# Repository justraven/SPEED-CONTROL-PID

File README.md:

# MOTOR DC SPEED CONTROL

Implementing PID control to regulate the speed of a DC motor.

## File Structure
```
📦CODE
 ┣ 📂lib
 ┃ ┣ 📂parsing
 ┃ ┃ ┗ 📜parsing.h
 ┣ 📂src
 ┃ ┗ 📜main.cpp
 📦GUI
 ┣ 📂LABVIEW
 ┃ ┣ 📜block_diagram.pdf
 ┃ ┣ 📜block_diagram_2.pdf
 ┃ ┣ 📜block_diagram_3.pdf
 ┃ ┣ 📜front_panel.pdf
 ┃ ┣ 📜front_panel_2.pdf
 ┃ ┣ 📜front_panel_3.pdf
 ┃ ┣ 📜GUI.vi
 ┃ ┣ 📜GUI_SubVi.vi
 ┃ ┣ 📜PID.txt
 ┃ ┣ 📜PID_2.txt
 ┃ ┣ 📜PID_3.txt
 ┃ ┗ 📜TEST.txt
 ┗ 📂LABVIEW LEGACY
 ┃ ┣ 📂GUI v2
 ┃ ┃ ┗ 📜GUI.vi
 ┃ ┣ 📂GUI v2.1
 ┃ ┃ ┗ 📜GUI.vi
 ┃ ┗ 📜GUI.vi
📦3D Case Design
 ┗ 📂Desain Mekanik Kendali Motor DC
 ┃ ┣ 📜Alas untuk Motor DC.DXF
 ┃ ┣ 📜Alas untuk Motor DC.SLDPRT
 ┃ ┣ 📜Couple Motor.jpeg
 ┃ ┣ 📜Desain Mekanik V1 Atas.PNG
 ┃ ┣ 📜Desain Mekanik V1 Depan.PNG
 ┃ ┣ 📜Desain Mekanik V1 Trimetric kiri.PNG
 ┃ ┣ 📜Desain Mekanik V1 Trimetric.PNG
 ┃ ┣ 📜Desain Mekanik V2 Atas.PNG
 ┃ ┣ 📜Desain Mekanik V2 Trimetric.PNG
 ┃ ┣ 📜Desain Mekanik V3 Atas.PNG
 ┃ ┣ 📜Desain Mekanik V3 Trimetric.PNG
 ┃ ┣ 📜holder motor dc.PNG
 ┃ ┣ 📜Holder Motor DC.SLDPRT
 ┃ ┣ 📜Holder Motor DC.STL
 ┃ ┣ 📜Kendali Motor DC.SLDASM
 ┃ ┣ 📜motor masuk holder.jpeg
 ┃ ┣ 📜Spacer.SLDPRT
 ┃ ┣ 📜SPEED CONTROL MOTOR DC.SLDASM
 ┃ ┣ 📜SPEED_CONTROL_2.step
 ┃ ┣ 📜SPEED_CONTROL_NEW.step
 ┃ ┗ 📜Terminal block TB-1503.SLDASM
 ```
 
## Software Used
- Vscode (with platformio extension)
- LabVIEW (for GUI, I use LabView 21)
- KiCad (I use ver 6.0.10)
- SolidWorks (for 3D modeling)

## Developed by
- Alim Satria [@justraven](https://github.com/justraven) (PCB Design, Firmware)
- Ilham Dwi Cahyo [@ilhamdwi754](https://github.com/ilhamdwi754) (3D Design)

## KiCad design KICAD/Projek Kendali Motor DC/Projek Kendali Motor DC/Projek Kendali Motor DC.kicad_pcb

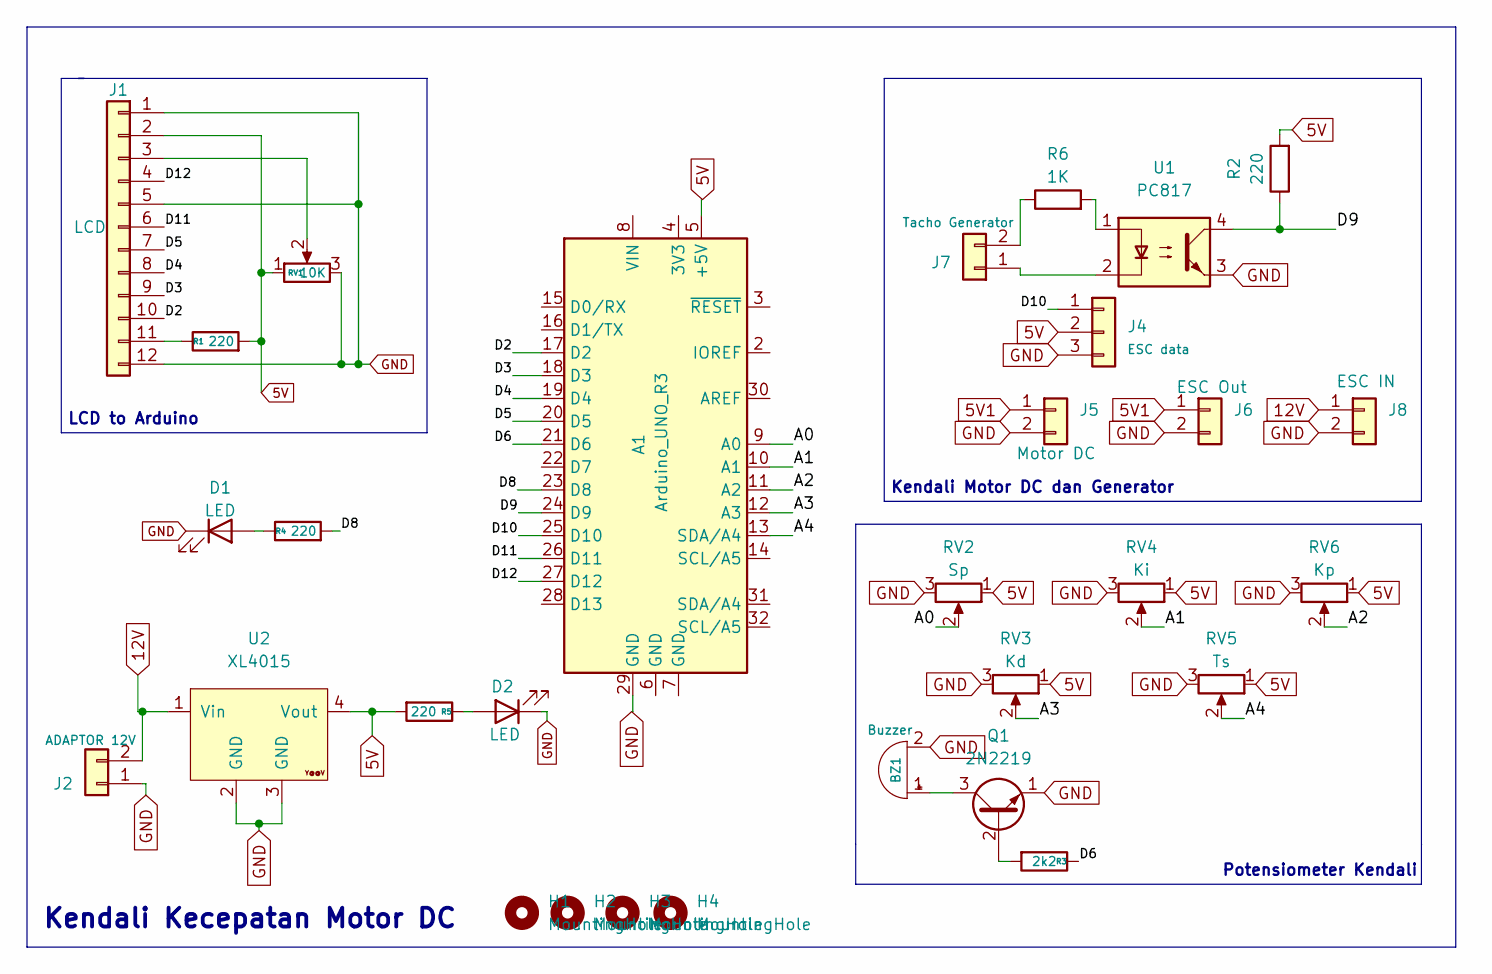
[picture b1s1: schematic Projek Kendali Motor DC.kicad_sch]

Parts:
A1: Arduino_UNO_R3; Arduino_UNO_R3_WithMountingHoles
BZ1: Buzzer; Buzzer_12x9.5RM7.6
D1, D2: LED; LED_D5.0mm
H1, H2, H3, H4: MountingHole; MountingHole_2.5mm_Pad_Via
J1: LCD; PinHeader_1x12_P2.54mm_Vertical
J2: ADAPTOR 12V; TerminalBlock_bornier-2_P5.08mm
J4: ESC data; PinHeader_1x03_P2.54mm_Vertical
J5: Motor DC; TerminalBlock_bornier-2_P5.08mm
J6: ESC Out; TerminalBlock_bornier-2_P5.08mm
J7: Tacho Generator; TerminalBlock_bornier-2_P5.08mm
J8: ESC IN; TerminalBlock_bornier-2_P5.08mm
Q1: 2N2219; TO-39-3
R1, R2, R4, R5: 220; R_Axial_DIN0207_L6.3mm_D2.5mm_P7.62mm_Horizontal
R3: 2k2; R_Axial_DIN0207_L6.3mm_D2.5mm_P7.62mm_Horizontal
R6: 1K; R_Axial_DIN0207_L6.3mm_D2.5mm_P7.62mm_Horizontal
RV1: 10K; Potentiometer_Piher_PC-16_Single_Horizontal
RV2: Sp; Potentiometer_Piher_PC-16_Single_Horizontal
RV3: Kd; Potentiometer_Piher_PC-16_Single_Horizontal
RV4: Ki; Potentiometer_Piher_PC-16_Single_Horizontal
RV5: Ts; Potentiometer_Piher_PC-16_Single_Horizontal
RV6: Kp; Potentiometer_Piher_PC-16_Single_Horizontal
U1: PC817; DIP-4_W7.62mm
U2: XL4015; YAAJ_DCDC_StepDown_LM2596

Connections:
5V: A1.5 (+5V), J1.2, J4.2, R1.2, R2.2, R5.2, RV1.1, RV2.1, RV3.1, RV4.1, RV5.1, RV6.1, U2.4 (Vout); also elsewhere on the board
5V1: J5.1, J6.1
12V: J2.2, J8.1, U2.1 (Vin)
/A0: A1.9 (A0), RV2.2
/A1: A1.10 (A1), RV4.2
/A2: A1.11 (A2), RV6.2
/A3: A1.12 (A3), RV3.2
/A4: A1.13 (SDA/A4), RV5.2
/D2: A1.17 (D2), J1.10
/D3: A1.18 (D3), J1.9
/D4: A1.19 (D4), J1.8
/D5: A1.20 (D5), J1.7
/D6: A1.21 (D6), R3.1
/D8: A1.23 (D8), R4.2
/D9: A1.24 (D9), R2.1, U1.4
/D10: A1.25 (D10), J4.1
/D11: A1.26 (D11), J1.6
/D12: A1.27 (D12), J1.4
GND: A1.29 (GND), BZ1.2 (+), D1.1 (K), D2.1 (K), J1.1, J1.5, J1.12, J2.1, J4.3, J5.2, J6.2, J8.2, Q1.1 (E), RV1.3, RV2.3, RV3.3, RV4.3, RV5.3, RV6.3, U1.3, U2.2 (GND), U2.3 (GND); also elsewhere on the board
unnamed: BZ1.1 (-), Q1.3 (C)
unnamed: D1.2 (A), R4.1
unnamed: D2.2 (A), R5.1
unnamed: J1.3, RV1.2
unnamed: J1.11, R1.1
unnamed: J7.2, R6.1
unnamed: Q1.2 (B), R3.2
unnamed: R6.2, U1.1
unnamed: J7.1, U1.2

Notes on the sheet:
Kendali Kecepatan Motor DC
Kendali Motor DC dan Generator
LCD to Arduino
Potensiometer Kendali

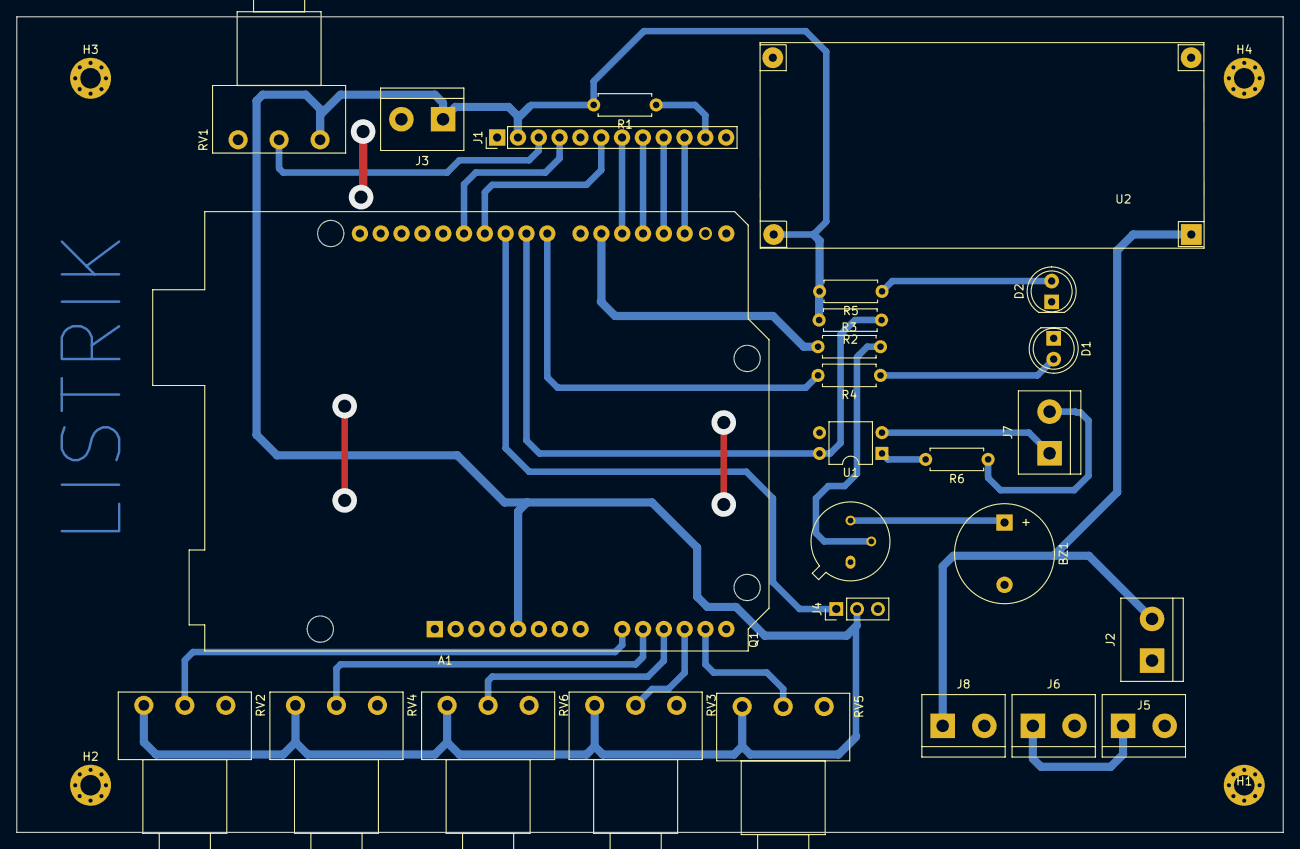
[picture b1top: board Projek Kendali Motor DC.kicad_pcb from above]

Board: 2 copper layers, 154.5 x 99.5 mm, 31 parts (0 on the bottom side), 28 nets.

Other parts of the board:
J3: Stepdown OUT; TerminalBlock_bornier-2_P5.08mm

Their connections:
5V: J3.1; also elsewhere on the board
GND: J3.2; also elsewhere on the board

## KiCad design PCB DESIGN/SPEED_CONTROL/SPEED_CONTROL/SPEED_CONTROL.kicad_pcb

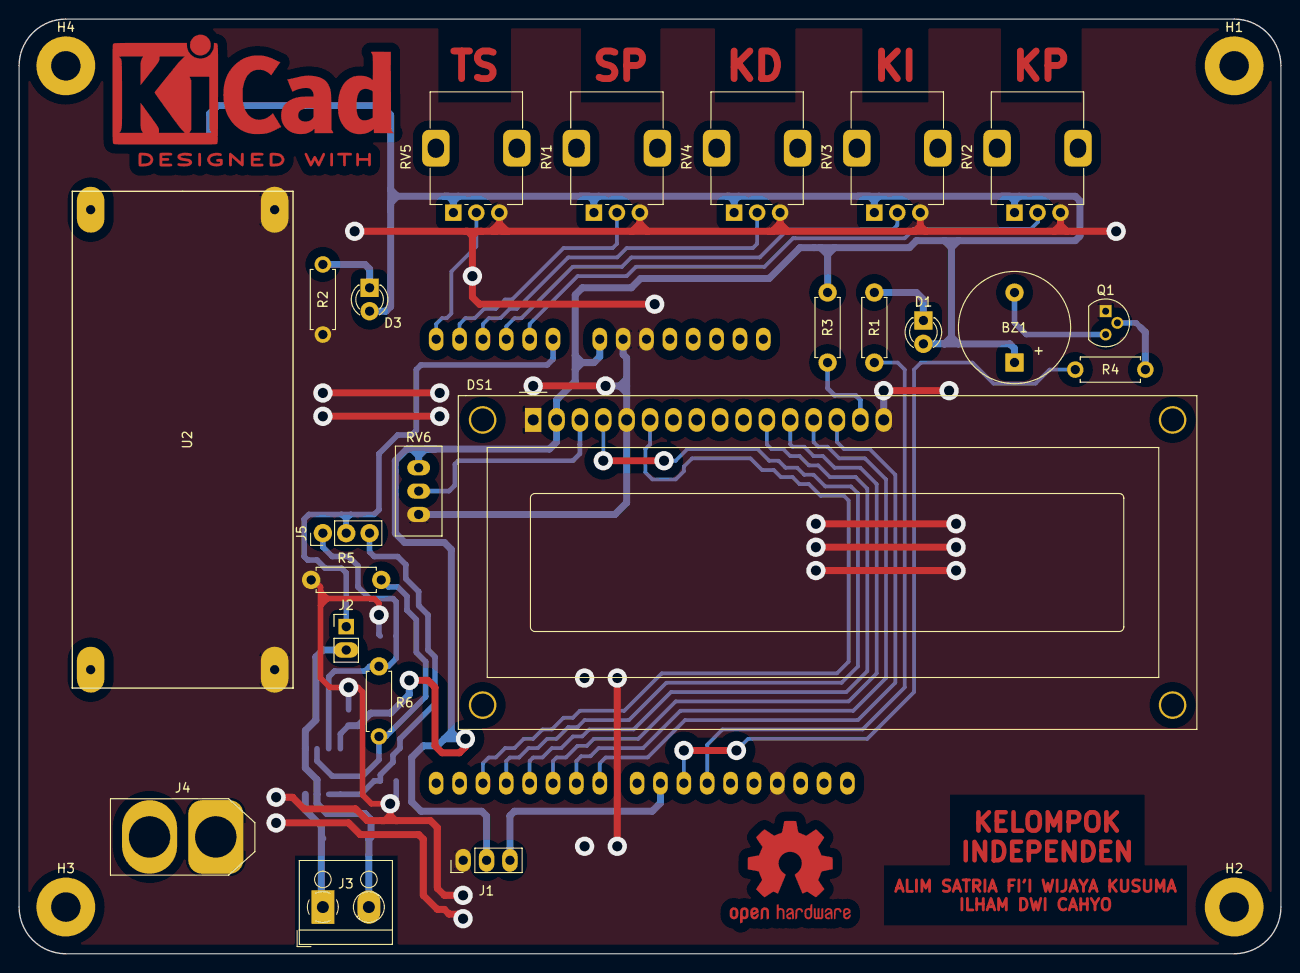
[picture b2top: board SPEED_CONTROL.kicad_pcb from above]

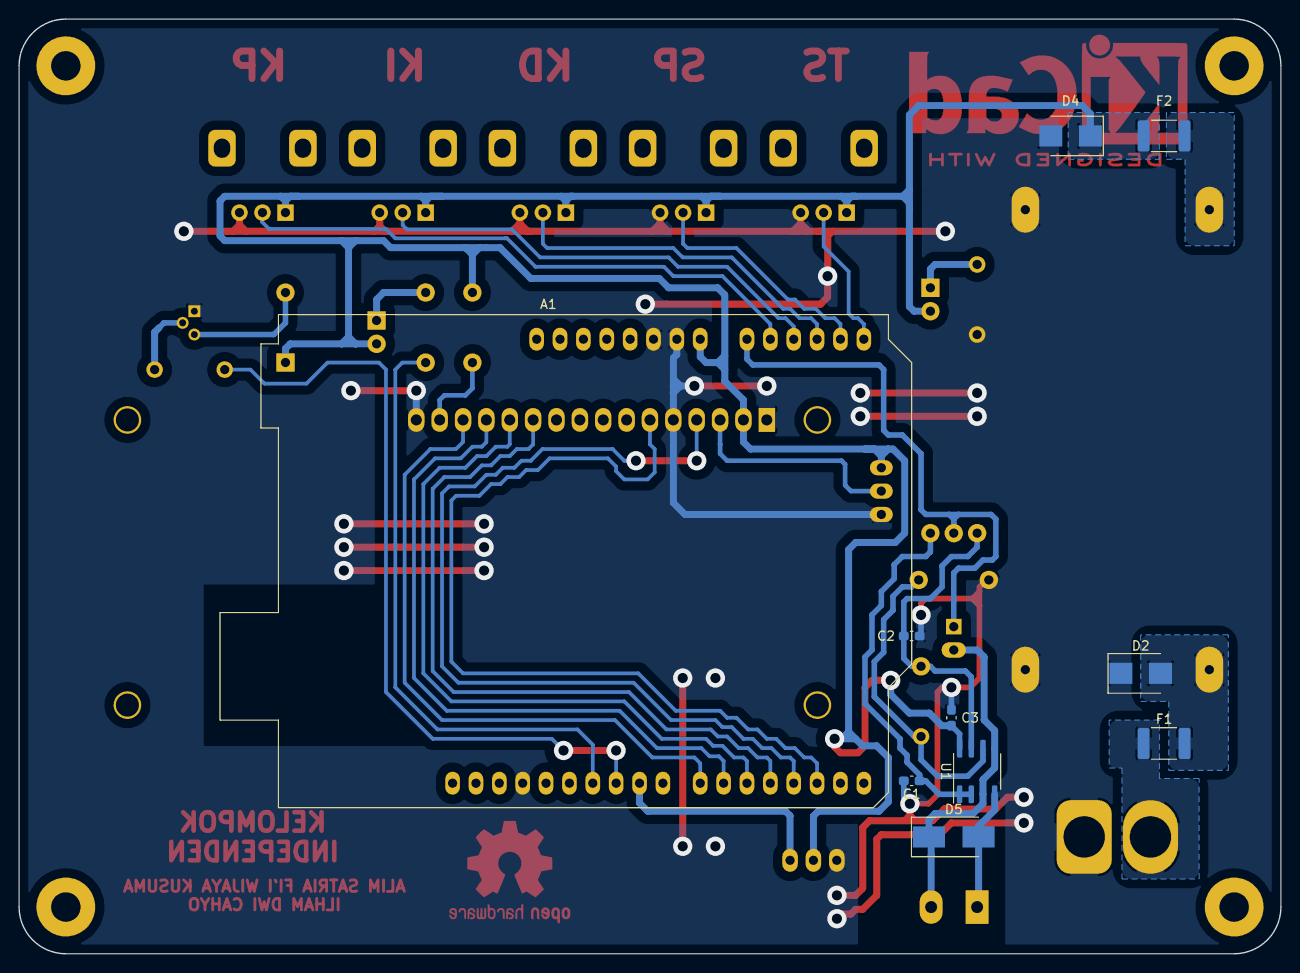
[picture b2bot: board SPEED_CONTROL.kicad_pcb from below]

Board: 2 copper layers, 137.2 x 101.6 mm, 37 parts (10 on the bottom side), 30 nets.

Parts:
A1: Arduino_UNO_R3
BZ1: Buzzer; MagneticBuzzer_ProSignal_ABI-009-RC
C1, C2: 0.1uF/100nF; C_0603_1608Metric_Pad1.08x0.95mm_HandSolder
C3: 0.1uF / 100nF; C_0603_1608Metric_Pad1.08x0.95mm_HandSolder
D1, D3: LED; LED_D3.0mm
D2: DIODE; D_SMB
D4: D; D_SMB
D5: D_Small; D_SMB_Handsoldering
DS1: WC1602A
F1: 16V/2A; Fuse_1812_4532Metric_Pad1.30x3.40mm_HandSolder
F2: 16V/02A; Fuse_1812_4532Metric_Pad1.30x3.40mm_HandSolder
H1, H2, H3, H4: MountingHole; MountingHole_3.2mm_M3_Pad
J1: ESC_PIN; PinHeader_1x03_P2.54mm_Vertical
J2: SEN_PIN; PinHeader_1x02_P2.54mm_Vertical
J3: Screw_Terminal_01x02; TerminalBlock_RND_205-00001_1x02_P5.00mm_Horizontal
J4: POWER CONN; AMASS_XT60-M_1x02_P7.20mm_Vertical
J5: SWITCH_SEN; PinHeader_1x03_P2.54mm_Vertical
Q1: 2N222; TO-92
R1, R2, R3: 330R; R_Axial_DIN0207_L6.3mm_D2.5mm_P7.62mm_Horizontal
R4: 1K; R_Axial_DIN0207_L6.3mm_D2.5mm_P7.62mm_Horizontal
R5: 10K; R_Axial_DIN0207_L6.3mm_D2.5mm_P7.62mm_Horizontal
R6: 20K; R_Axial_DIN0207_L6.3mm_D2.5mm_P7.62mm_Horizontal
RV1, RV2, RV3, RV4, RV5: 10K; Potentiometer_Alps_RK09K_Single_Vertical
RV6: 10K; Potentiometer_Bourns_3296W_Vertical
U1: LM358; SOIC-8_3.9x4.9mm_P1.27mm
U2: XL4015; XL4015_Converter

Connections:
+5V: A1.8 (VIN), BZ1.1 (-), C3.1, D1.2 (A), D3.2 (A), D4.1 (K), DS1.2 (VDD), F2.2, J1.2, R3.1, RV1.1, RV2.1, RV3.1, RV4.1, RV5.1, RV6.1, U1.8 (V+)
+12V: D2.2 (K), F1.2, U2.1 (IN+)
/BUZZER: A1.25 (D10), R4.1
/D4: A1.19 (D4), DS1.11 (D4)
/D5: A1.20 (D5), DS1.12 (D5)
/D6: A1.21 (D6), DS1.13 (D6)
/D7: A1.22 (D7), DS1.14 (D7)
/E: A1.17 (D2), DS1.6 (E)
/KD: A1.12 (A3), RV4.2
/KI: A1.11 (A2), RV3.2
/KP: A1.10 (A1), RV2.2
/LED: A1.26 (D11), R1.2
/MOTOR_SEN: D5.1 (K), J2.2, J3.2, U1.3 (+), U1.5 (+)
/PWM: A1.24 (D9), J1.3
/RS: A1.18 (D3), DS1.4 (RS)
/SP: A1.13 (SDA/A4), RV1.2
/TACHO: A1.9 (A0), J2.1, J5.2
/TACHO_1: C1.1, J5.3, U1.1, U1.2 (-)
/TACHO_2: C2.1, J5.1, R6.2, U1.7
/TS: A1.14 (SCL/A5), RV5.2
GND: A1.6 (GND), A1.7 (GND), A1.29 (GND), C1.2, C2.2, C3.2, D2.1 (A), D4.2 (A), D5.2 (A), DS1.1 (VSS), DS1.5 (R/W), DS1.16 (LED(-)), J1.1, J3.1, J4.1, Q1.1 (E), R2.2, R5.1, RV1.3, RV2.3, RV3.3, RV4.3, RV5.3, RV6.3, U1.4 (V-), U2.2 (IN-), U2.4 (OUT-)
unnamed: BZ1.2 (+), Q1.3 (C)
unnamed: D1.1 (K), R1.1
unnamed: D3.1 (K), R2.1
unnamed: DS1.3 (VO), RV6.2
unnamed: DS1.15 (LED(+)), R3.2
unnamed: F2.1, U2.3 (OUT+)
unnamed: F1.1, J4.2
unnamed: Q1.2 (B), R4.2
unnamed: R5.2, R6.1, U1.6 (-)

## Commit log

2022-12-21 add files
    add PCB Design file, code, and GUI program
2022-12-22 remove some file
2022-12-22 add PCB schematic documentation
2022-12-28 add support
    Add support for older version of labview
2023-01-18 add identification system on matlab
2023-01-20 smoothing signal and add stability
    - Change baud rate to 115200
    - Change moving average filter coefficient to 200
    - Update on LabView Serial Communication
2023-01-31 add 3D model with PCB track
2023-02-02 tyding up folders
2023-06-05 backup
2023-06-20 add 3D Model
